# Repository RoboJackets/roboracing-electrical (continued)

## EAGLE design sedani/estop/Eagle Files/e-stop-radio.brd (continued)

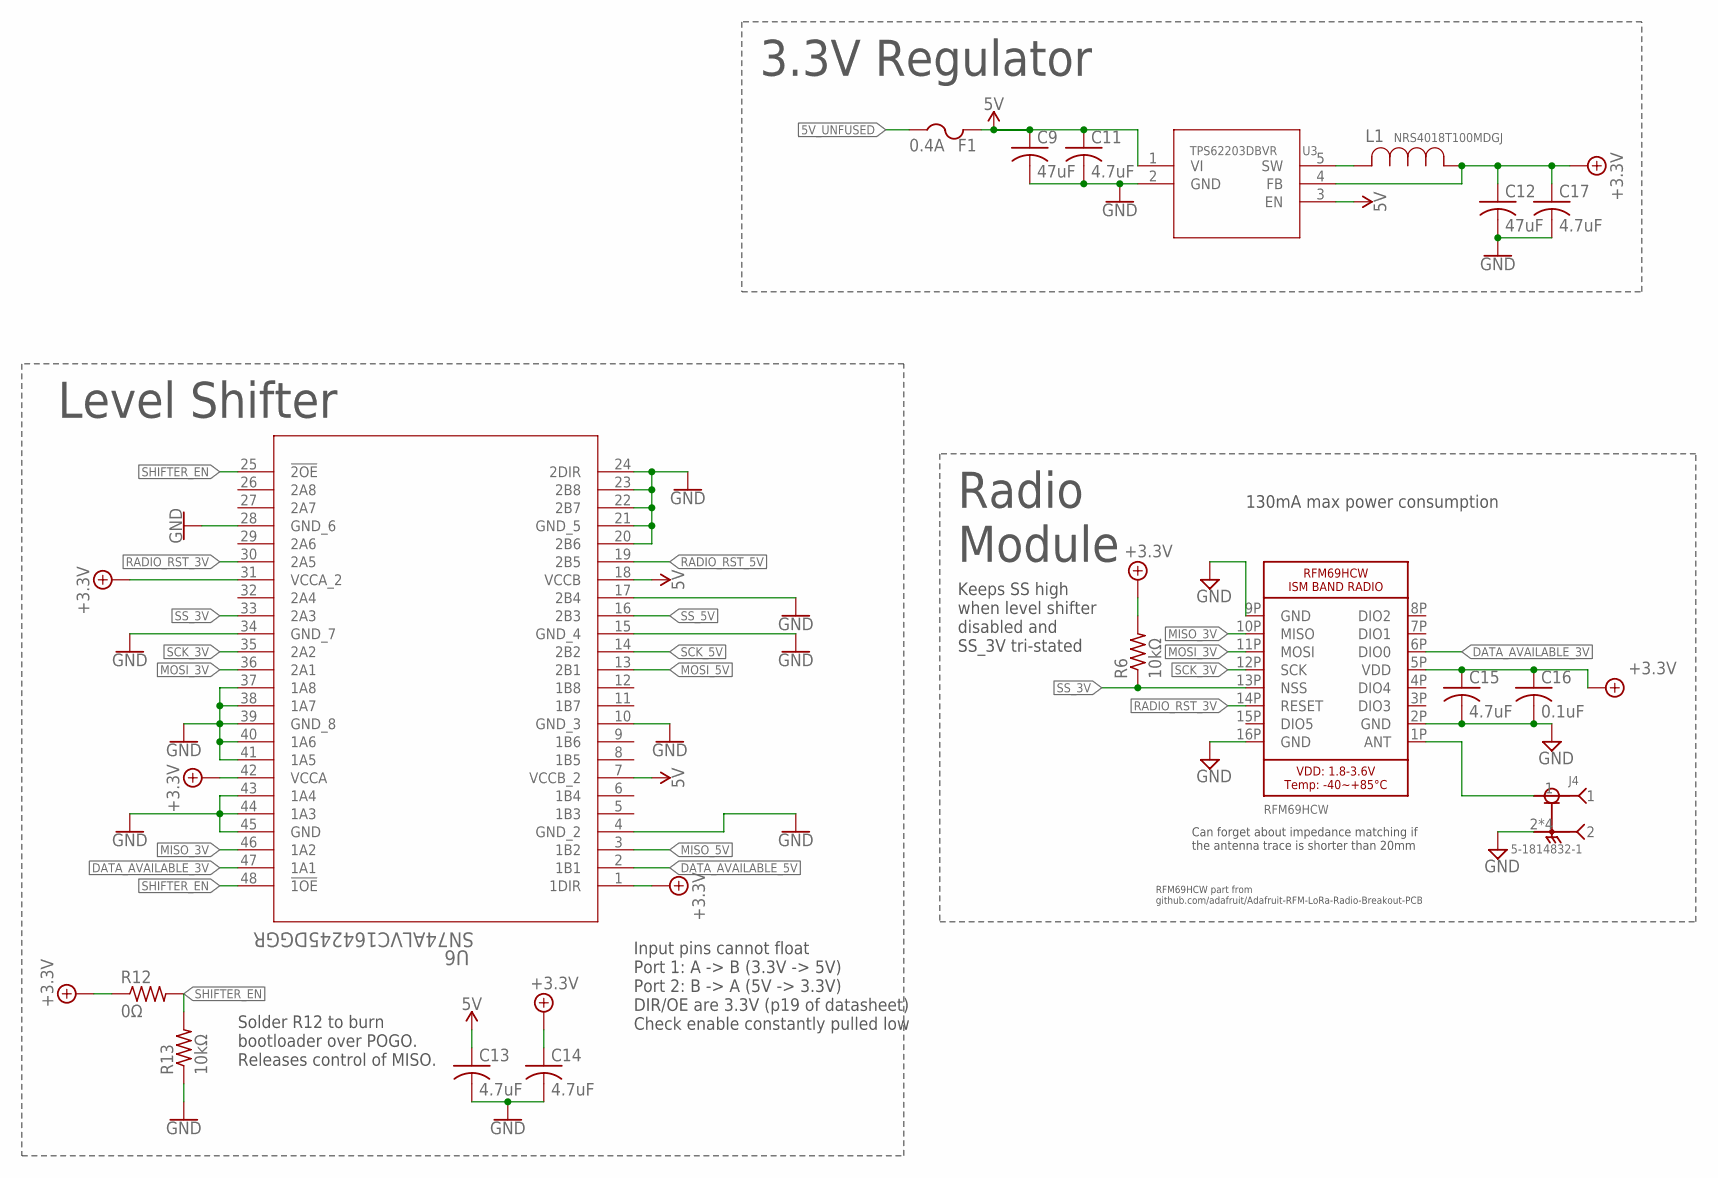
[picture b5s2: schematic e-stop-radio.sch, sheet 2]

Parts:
C9, C12: 47uF; C1206
C11, C13, C14, C15, C17: 4.7uF; C0603
C16: 0.1uF; C0603
F1: 0.4A; R1206
J4: 5-1814832-1; TE_5-1814832-1
L1: NRS4018T100MDGJ; IND_TAIYO_NRS4018
R6, R13: 10kΩ; R0603
R12: 0Ω; R0603
U3: TPS62203DBVR; DBV5
U5: RFM69HCW; RFMHCW_SMT
U6: SN74ALVC164245DGGR; DGG48

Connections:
5V: C9.1, C11.1, C13.1, F1.2, U3.1 (VI), U3.3 (EN), U6.7 (VCCB_2), U6.18 (VCCB); also elsewhere on the board
5V_UNFUSED: F1.1; also elsewhere on the board
+3.3V: C12.1, C14.1, C15.1, C16.1, C17.1, L1.1, R6.2, R12.1, U3.4 (FB), U5.5P (VDD), U6.1 (1DIR), U6.31 (VCCA_2), U6.42 (VCCA); also elsewhere on the board
DATA_AVAILABLE_3V: U5.6P (DIO0), U6.47 (1A1)
DATA_AVAILABLE_5V: U6.2 (1B1); also elsewhere on the board
GND: C9.2, C11.2, C12.2, C13.2, C14.2, C15.2, C16.2, C17.2, J4.2, J4.3 (2), J4.4 (2), J4.5 (2), R13.1, U3.2 (GND), U5.2P (GND), U5.9P (GND), U5.16P (GND), U6.4 (GND_2), U6.10 (GND_3), U6.15 (GND_4), U6.17 (2B4), U6.20 (2B6), U6.21 (GND_5), U6.22 (2B7), U6.23 (2B8), U6.24 (2DIR), U6.28 (GND_6), U6.34 (GND_7), U6.37 (1A8), U6.38 (1A7), U6.39 (GND_8), U6.40 (1A6), U6.41 (1A5), U6.43 (1A4), U6.44 (1A3), U6.45 (GND); also elsewhere on the board
MISO_3V: U5.10P (MISO), U6.46 (1A2)
MISO_5V: U6.3 (1B2); also elsewhere on the board
MOSI_3V: U5.11P (MOSI), U6.36 (2A1)
MOSI_5V: U6.13 (2B1); also elsewhere on the board
unnamed: L1.2, U3.5 (SW)
RADIO_RST_3V: U5.14P (RESET), U6.30 (2A5)
RADIO_RST_5V: U6.19 (2B5); also elsewhere on the board
RF_SIGNAL: J4.1, U5.1P (ANT)
SCK_3V: U5.12P (SCK), U6.35 (2A2)
SCK_5V: U6.14 (2B2); also elsewhere on the board
SHIFTER_EN: R12.2, R13.2, U6.25 (!2OE), U6.48 (!1OE)
SS_3V: R6.1, U5.13P (NSS), U6.33 (2A3)
SS_5V: U6.16 (2B3); also elsewhere on the board

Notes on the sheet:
RFM69HCW part from github.com/adafruit/Adafruit-RFM-LoRa-Radio-Breakout-PCB
130mA max power consumption
Radio Module
Can forget about impedance matching if the antenna trace is shorter than 20mm
3.3V Regulator
Level Shifter
Solder R12 to burn bootloader over POGO. Releases control of MISO.
Input pins cannot float Port 1: A -> B (3.3V -> 5V) Port 2: B -> A (5V -> 3.3V) DIR/OE are 3.3V (p19 of datasheet) Check enable constantly pulled low
Keeps SS high when level shifter disabled and SS_3V tri-stated

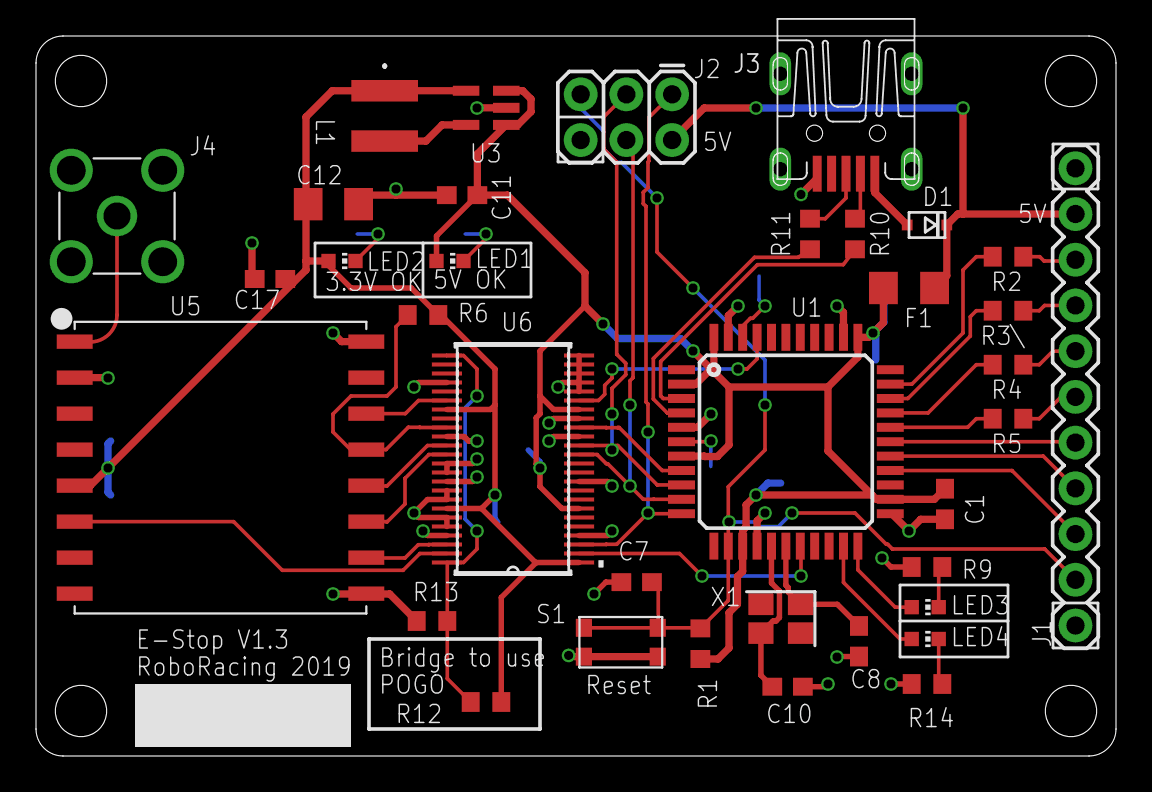
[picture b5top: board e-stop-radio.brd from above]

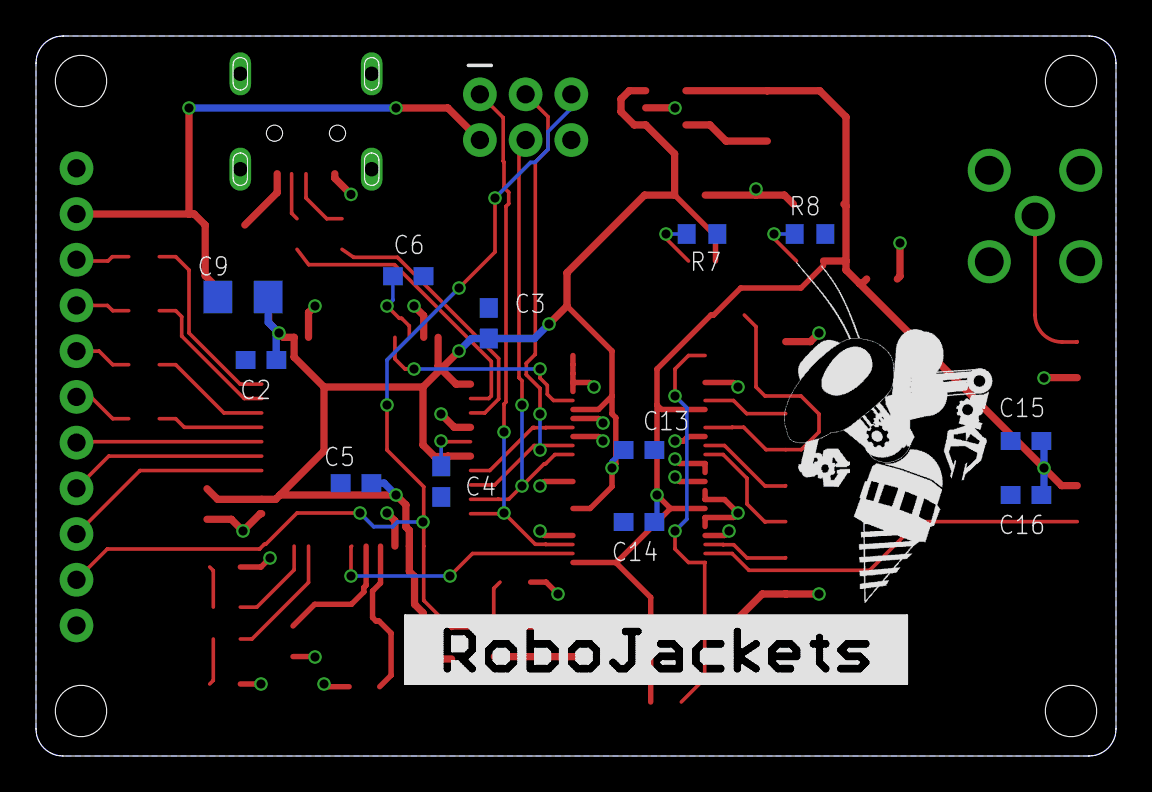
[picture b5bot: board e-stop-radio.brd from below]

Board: 2 copper layers, 60.0 x 40.0 mm, 50 parts (14 on the bottom side), 46 nets.

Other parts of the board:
U$1: ROBOBUZZ_1.0X
U$2: ROBOJACKETS
